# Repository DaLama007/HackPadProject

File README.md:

## My HackPad

**KeyLayout**
1st key -> Windows Bttn + D (window hider)
2nd key -> CTRL+ SHIFT + M (DIscord Mute)
3rd key -> Right Mouse Bttn Click, then Q (Devtools firefox)
Rotary encoder -> scroll down/up
Display -> Bongo Cat

Render of expected final product

Schematic of the circuit

Picture of PCB 

Picture of Case

# Bill of Materials (BOM)

| Component | Qty |
|-----------|-----|
| Seeed XIAO RP2040 Microcontroller | 1 |
| MX-Style Mechanical Switches | 3 |
| EC11 Rotary Encoder (20mm D-Shaft) | 1 |
| 0.91" 128×32 OLED Display | 1 |
| Blank DSA Keycaps | 3 |
| SK6812 MINI-E RGB LEDs | 3 |
| M3×16mm Screws | 4 |
| M3×5×4mm Heatset Inserts | 4 |
| PCB (JLCPCB fabrication) | 1 |
| 3D Printed Case (Gift card) | 1 |
| Soldering iron (Gift card) | 1 |

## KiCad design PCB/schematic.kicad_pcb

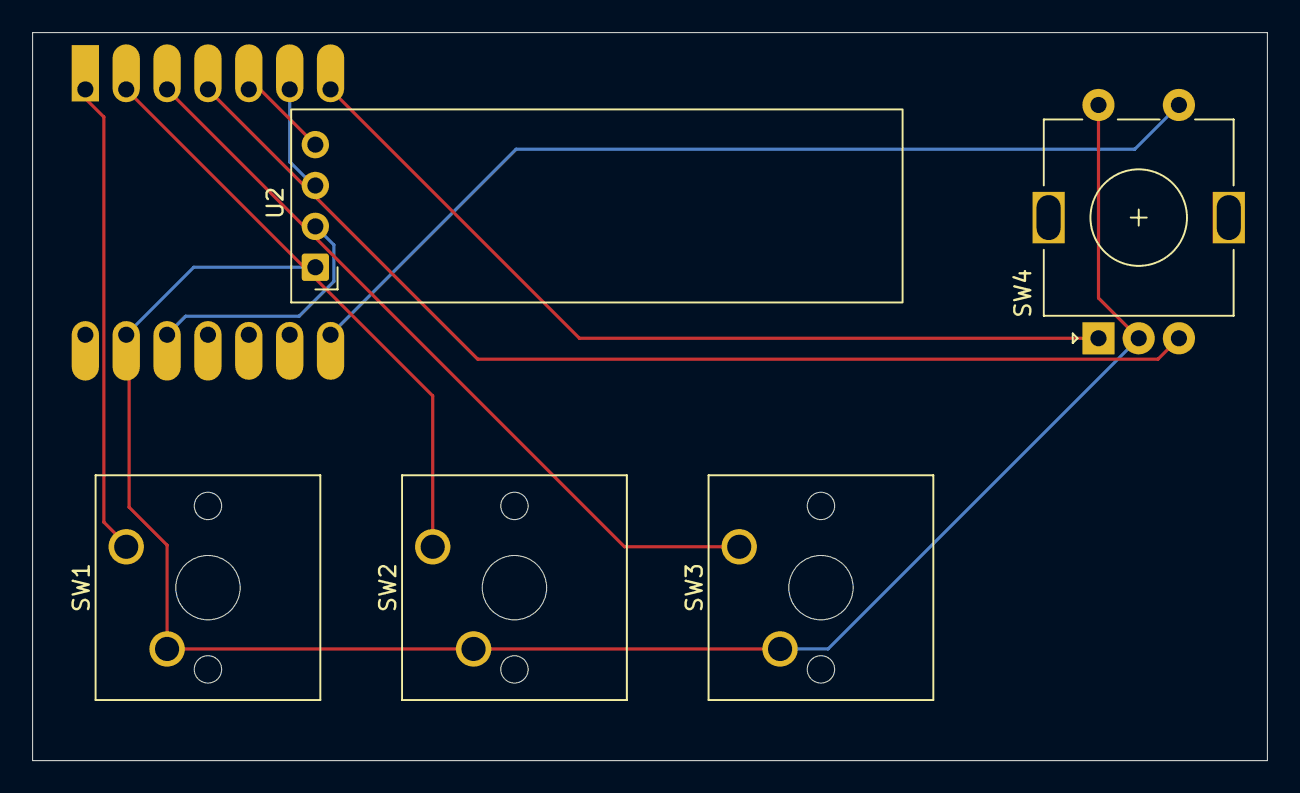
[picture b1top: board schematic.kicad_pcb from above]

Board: 2 copper layers, 76.7 x 45.2 mm, 6 parts (1 on the bottom side), 10 nets.

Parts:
SW1, SW2, SW3: SW_Push; SW_Cherry_MX_1.00u_PCB
SW4: RotaryEncoder_Switch; RotaryEncoder_Alps_EC11E-Switch_Vertical_H20mm
U1: MOUDLE-SEEEDUINO-XIAO; XIAO-Generic-Hybrid-14P-2.54-21X17.8MM
U2: ER_OLEDM0.91_1x-I2C

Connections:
+3.3V: U1.12 (3V3), U2.2 (VCC)
GND: SW1.2, SW2.2, SW3.2, SW4.C, SW4.S2, U1.13 (GND), U2.1 (GND)
unnamed: SW1.1, U1.1 (PA02_A0_D0)
unnamed: SW2.1, U1.2 (PA4_A1_D1)
unnamed: U1.5 (PA8_A4_D4_SDA), U2.4 (SDA)
unnamed: U1.6 (PA9_A5_D5_SCL), U2.3 (SCL)
unnamed: SW3.1, U1.3 (PA10_A2_D2)
unnamed: SW4.B, U1.4 (PA11_A3_D3)
unnamed: SW4.A, U1.7 (PB08_A6_D6_TX)
unnamed: SW4.S1, U1.8 (PB09_A7_D7_RX)

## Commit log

2026-06-07 Create dfx file, schematic for the pcb.
2026-06-07 Generate gerber files to add to gerber folder and zip.
2026-06-08 Finish the whole model for the case of the keyboard and save as individual files(bottomBox, topBox)
2026-06-08 Rename of the files to be acording to stardance demand
2026-06-11 Add info file, rules and then the keymap to define actions for keyboard.
2026-06-11 Add rotary encoder to the configuration and also the keymap code.
2026-06-11 Add firmware code for the display.
2026-06-11 Update folder names and reorder files according to the stardance convention.
2026-06-12 Add readme.md
2026-06-12 Add details to the readme for context over the keys.
2026-06-13 Complete revamp of the 3d models due to precision mistakes repaired using 3d models of mechanical parts. Minor chnages to readme.
